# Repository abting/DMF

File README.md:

# DMF
DMF Arduino Software &amp; UI

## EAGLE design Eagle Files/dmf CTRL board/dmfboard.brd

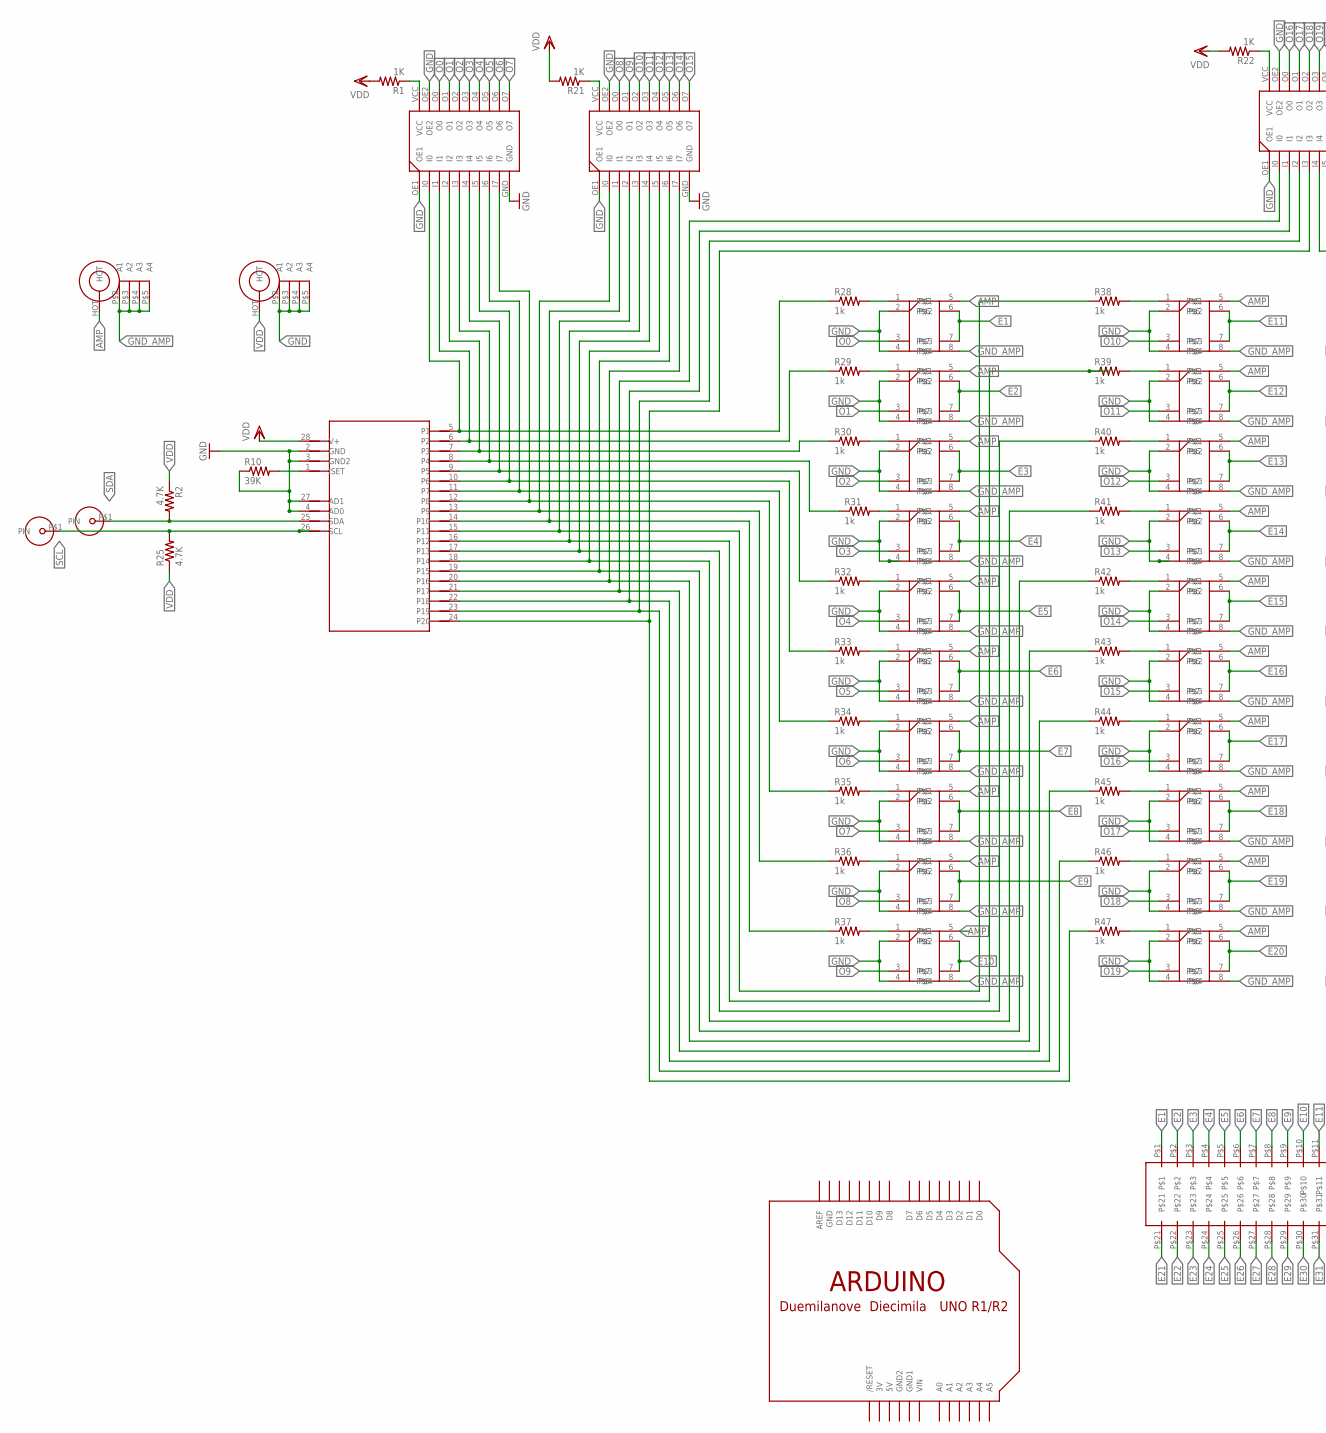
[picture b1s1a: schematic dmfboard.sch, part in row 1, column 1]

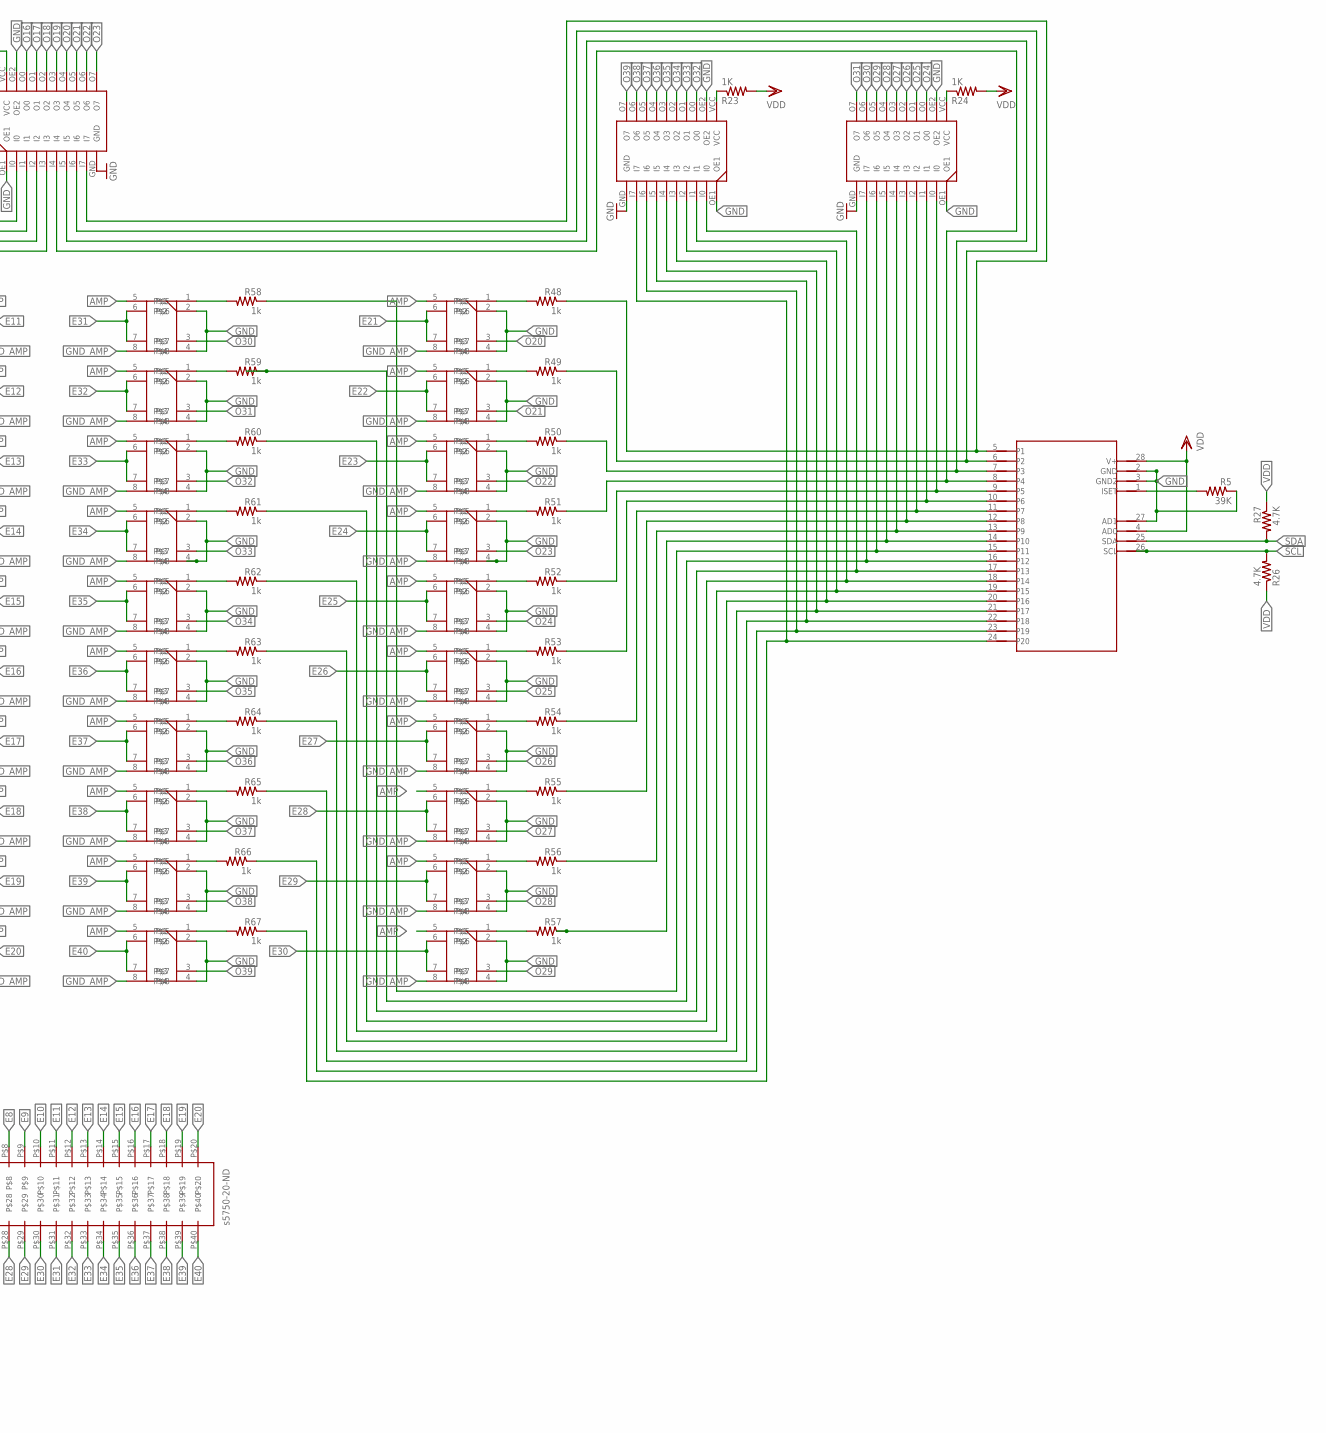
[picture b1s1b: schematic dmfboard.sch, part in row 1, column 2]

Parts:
+5V: BNC-BNC
AMP: BNC-BNC
INVERTOR1, INVERTOR2, INVERTOR3, INVERTOR4: 74AC540; SO20W
INVERTTOR5: 74AC540; SO20W
MAX1, MAX2: MAX7300; QSOP24
P1, P2, P3, P4, P5, P6, P7, P8, P9, P10, P11, P12, P13, P14, P15, P16, P17, P18, P19, P20, P21, P22, P23, P24, P25, P26, P27, P28, P29, P30, P31, P32, P33, P34, P35, P36, P37, P38, P39, P40: AQW21; AQW216EH
R1, R21, R22, R23, R24: 1K; M0805
R2, R25, R26, R27: 4.7K; M0805
R5, R10: 39K; M0805
R28, R29, R30, R31, R32, R33, R34, R35, R36, R37, R38, R39, R40, R41, R42, R43, R44, R45, R46, R47, R48, R49, R50, R51, R52, R53, R54, R55, R56, R57, R58, R59, R60, R61, R62, R63, R64, R65, R66, R67: 1k; M0805
SCL: TH_HOLE; TH_PIN
SDA: TH_HOLE; TH_PIN
U$1: ARDUINO-NODIM
U$50: S5750_20_ND40PIN_CONNECTOR; S5750-20_ND

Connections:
3V: U$1.3V
5V: U$1.5V
AMP: AMP.HOT, P1.5, P2.5, P3.5, P4.5, P5.5, P6.5, P7.5, P8.5, P9.5, P10.5, P11.5, P12.5, P13.5, P14.5, P15.5, P16.5, P17.5, P18.5, P19.5, P20.5, P21.5, P22.5, P23.5, P24.5, P25.5, P26.5, P27.5, P28.5, P29.5, P30.5, P31.5, P32.5, P33.5, P34.5, P35.5, P36.5, P37.5, P38.5, P39.5, P40.5
E1: P1.6, P1.7, U$50.P$1
E2: P2.6, P2.7, U$50.P$2
E3: P3.6, P3.7, U$50.P$3
E4: P4.6, P4.7, U$50.P$4
E5: P5.6, P5.7, U$50.P$5
E6: P6.6, P6.7, U$50.P$6
E7: P7.6, P7.7, U$50.P$7
E8: P8.6, P8.7, U$50.P$8
E9: P9.6, P9.7, U$50.P$9
E10: P10.6, P10.7, U$50.P$10
E11: P11.6, P11.7, U$50.P$11
E12: P12.6, P12.7, U$50.P$12
E13: P13.6, P13.7, U$50.P$13
E14: P14.6, P14.7, U$50.P$14
E15: P15.6, P15.7, U$50.P$15
E16: P16.6, P16.7, U$50.P$16
E17: P17.6, P17.7, U$50.P$17
E18: P18.6, P18.7, U$50.P$18
E19: P19.6, P19.7, U$50.P$19
E20: P20.6, P20.7, U$50.P$20
E21: P21.6, P21.7, U$50.P$21
E22: P22.6, P22.7, U$50.P$22
E23: P23.6, P23.7, U$50.P$23
E24: P24.6, P24.7, U$50.P$24
E25: P25.6, P25.7, U$50.P$25
E26: P26.6, P26.7, U$50.P$26
E27: P27.6, P27.7, U$50.P$27
E28: P28.6, P28.7, U$50.P$28
E29: P29.6, P29.7, U$50.P$29
E30: P30.6, P30.7, U$50.P$30
E31: P31.6, P31.7, U$50.P$31
E32: P32.6, P32.7, U$50.P$32
E33: P33.6, P33.7, U$50.P$33
E34: P34.6, P34.7, U$50.P$34
E35: P35.6, P35.7, U$50.P$35
E36: P36.6, P36.7, U$50.P$36
E37: P37.6, P37.7, U$50.P$37
E38: P38.6, P38.7, U$50.P$38
E39: P39.6, P39.7, U$50.P$39
E40: P40.6, P40.7, U$50.P$40
GND: +5V.P$2 (A1), +5V.P$3 (A2), +5V.P$4 (A3), +5V.P$5 (A4), INVERTOR1.GND, INVERTOR1.OE1, INVERTOR1.OE2, INVERTOR2.GND, INVERTOR2.OE1, INVERTOR2.OE2, INVERTOR3.GND, INVERTOR3.OE1, INVERTOR3.OE2, INVERTOR4.GND, INVERTOR4.OE1, INVERTOR4.OE2, INVERTTOR5.GND, INVERTTOR5.OE1, INVERTTOR5.OE2, MAX1.2 (GND), MAX1.3 (GND2), MAX1.4 (AD0), MAX1.27 (AD1), MAX2.2 (GND), MAX2.3 (GND2), MAX2.27 (AD1), P1.2, P1.4, P2.2, P2.4, P3.2, P3.4, P4.2, P4.4, P5.2, P5.4, P6.2, P6.4, P7.2, P7.4, P8.2, P8.4, P9.2, P9.4, P10.2, P10.4, P11.2, P11.4, P12.2, P12.4, P13.2, P13.4, P14.2, P14.4, P15.2, P15.4, P16.2, P16.4, P17.2, P17.4, P18.2, P18.4, P19.2, P19.4, P20.2, P20.4, P21.2, P21.4, P22.2, P22.4, P23.2, P23.4, P24.2, P24.4, P25.2, P25.4, P26.2, P26.4, P27.2, P27.4, P28.2, P28.4, P29.2, P29.4, P30.2, P30.4, P31.2, P31.4, P32.2, P32.4, P33.2, P33.4, P34.2, P34.4, P35.2, P35.4, P36.2, P36.4, P37.2, P37.4, P38.2, P38.4, P39.2, P39.4, P40.2, P40.4, R5.1, R10.1, U$1.GND
GND1: U$1.GND1
GND2: U$1.GND2
GND_AMP: AMP.P$2 (A1), AMP.P$3 (A2), AMP.P$4 (A3), AMP.P$5 (A4), P1.8, P2.8, P3.8, P4.8, P5.8, P6.8, P7.8, P8.8, P9.8, P10.8, P11.8, P12.8, P13.8, P14.8, P15.8, P16.8, P17.8, P18.8, P19.8, P20.8, P21.8, P22.8, P23.8, P24.8, P25.8, P26.8, P27.8, P28.8, P29.8, P30.8, P31.8, P32.8, P33.8, P34.8, P35.8, P36.8, P37.8, P38.8, P39.8, P40.8
unnamed: MAX2.1 (ISET), R5.2
unnamed: MAX1.1 (ISET), R10.2
unnamed: INVERTOR1.VCC, R1.1
unnamed: INVERTOR2.VCC, R21.1
unnamed: INVERTOR3.VCC, R22.1
unnamed: INVERTOR4.VCC, R23.1
unnamed: INVERTTOR5.VCC, R24.1
unnamed: P10.1, R37.2
unnamed: P9.1, R36.2
unnamed: P8.1, R35.2
unnamed: P7.1, R34.2
unnamed: P6.1, R33.2
unnamed: P5.1, R32.2
unnamed: P4.1, R31.2
unnamed: P3.1, R30.2
unnamed: P2.1, R29.2
unnamed: P1.1, R28.2
unnamed: P11.1, R38.2
unnamed: P12.1, R39.2
unnamed: P13.1, R40.2
unnamed: P14.1, R41.2
unnamed: P15.1, R42.2
unnamed: P16.1, R43.2
unnamed: P17.1, R44.2
unnamed: P18.1, R45.2
unnamed: P19.1, R46.2
unnamed: P20.1, R47.2
unnamed: INVERTOR1.I0, MAX1.5 (P1), R28.1
unnamed: INVERTOR1.I2, MAX1.7 (P3), R30.1
unnamed: INVERTOR1.I3, MAX1.8 (P4), R31.1
unnamed: INVERTOR1.I4, MAX1.9 (P5), R32.1
unnamed: INVERTOR1.I5, MAX1.10 (P6), R33.1
unnamed: INVERTOR1.I6, MAX1.11 (P7), R34.1
unnamed: INVERTOR1.I7, MAX1.12 (P8), R35.1
unnamed: INVERTOR2.I0, MAX1.13 (P9), R36.1
unnamed: INVERTOR2.I1, MAX1.14 (P10), R37.1
unnamed: INVERTOR2.I2, MAX1.15 (P11), R38.1
unnamed: INVERTOR2.I3, MAX1.16 (P12), R39.1
unnamed: INVERTOR2.I4, MAX1.17 (P13), R40.1
unnamed: INVERTOR2.I5, MAX1.18 (P14), R41.1
unnamed: INVERTOR2.I6, MAX1.19 (P15), R42.1
unnamed: INVERTOR2.I7, MAX1.20 (P16), R43.1
unnamed: INVERTOR3.I0, MAX1.21 (P17), R44.1
unnamed: INVERTOR3.I1, MAX1.22 (P18), R45.1
unnamed: INVERTOR3.I2, MAX1.23 (P19), R46.1
unnamed: INVERTOR3.I3, MAX1.24 (P20), R47.1
unnamed: INVERTOR1.I1, MAX1.6 (P2), R29.1
unnamed: P21.1, R48.2
unnamed: P22.1, R49.2
unnamed: P23.1, R50.2
unnamed: P24.1, R51.2
unnamed: P25.1, R52.2
unnamed: P26.1, R53.2
unnamed: P27.1, R54.2
unnamed: P28.1, R55.2
unnamed: P29.1, R56.2
unnamed: P30.1, R57.2
unnamed: INVERTTOR5.I0, MAX2.9 (P5), R52.1
unnamed: P31.1, R58.2
unnamed: P32.1, R59.2
unnamed: P33.1, R60.2
unnamed: P34.1, R61.2
unnamed: P35.1, R62.2
unnamed: P36.1, R63.2
unnamed: P37.1, R64.2
unnamed: P38.1, R65.2
unnamed: P39.1, R66.2
unnamed: P40.1, R67.2
unnamed: INVERTTOR5.I7, MAX2.16 (P12), R59.1
unnamed: INVERTTOR5.I1, MAX2.10 (P6), R53.1
unnamed: INVERTTOR5.I2, MAX2.11 (P7), R54.1
unnamed: INVERTTOR5.I3, MAX2.12 (P8), R55.1
unnamed: INVERTTOR5.I4, MAX2.13 (P9), R56.1
unnamed: INVERTTOR5.I5, MAX2.14 (P10), R57.1
unnamed: INVERTTOR5.I6, MAX2.15 (P11), R58.1
unnamed: INVERTOR4.I2, MAX2.19 (P15), R62.1
unnamed: INVERTOR4.I0, MAX2.17 (P13), R60.1
unnamed: INVERTOR4.I1, MAX2.18 (P14), R61.1
unnamed: INVERTOR4.I3, MAX2.20 (P16), R63.1
unnamed: INVERTOR4.I4, MAX2.21 (P17), R64.1
unnamed: INVERTOR4.I5, MAX2.22 (P18), R65.1
unnamed: INVERTOR4.I6, MAX2.23 (P19), R66.1
unnamed: INVERTOR4.I7, MAX2.24 (P20), R67.1
unnamed: INVERTOR3.I7, MAX2.5 (P1), R48.1
unnamed: INVERTOR3.I6, MAX2.6 (P2), R49.1
unnamed: INVERTOR3.I5, MAX2.7 (P3), R50.1
unnamed: INVERTOR3.I4, MAX2.8 (P4), R51.1
O0: INVERTOR1.O0, P1.3
O1: INVERTOR1.O1, P2.3
O2: INVERTOR1.O2, P3.3
O3: INVERTOR1.O3, P4.3
O4: INVERTOR1.O4, P5.3
O5: INVERTOR1.O5, P6.3
O6: INVERTOR1.O6, P7.3
O7: INVERTOR1.O7, P8.3
O8: INVERTOR2.O0, P9.3
O9: INVERTOR2.O1, P10.3
O10: INVERTOR2.O2, P11.3
O11: INVERTOR2.O3, P12.3
O12: INVERTOR2.O4, P13.3
O13: INVERTOR2.O5, P14.3
O14: INVERTOR2.O6, P15.3
O15: INVERTOR2.O7, P16.3
O16: INVERTOR3.O0, P17.3
O17: INVERTOR3.O1, P18.3
O18: INVERTOR3.O2, P19.3
O19: INVERTOR3.O3, P20.3
O20: INVERTOR3.O4, P21.3
O21: INVERTOR3.O5, P22.3
O22: INVERTOR3.O6, P23.3
O23: INVERTOR3.O7, P24.3
O24: INVERTTOR5.O0, P25.3
O25: INVERTTOR5.O1, P26.3
O26: INVERTTOR5.O2, P27.3
O27: INVERTTOR5.O3, P28.3
O28: INVERTTOR5.O4, P29.3
O29: INVERTTOR5.O5, P30.3
O30: INVERTTOR5.O6, P31.3
O31: INVERTTOR5.O7, P32.3
O32: INVERTOR4.O0, P33.3
O33: INVERTOR4.O1, P34.3
O34: INVERTOR4.O2, P35.3
O35: INVERTOR4.O3, P36.3
O36: INVERTOR4.O4, P37.3
O37: INVERTOR4.O5, P38.3
O38: INVERTOR4.O6, P39.3
O39: INVERTOR4.O7, P40.3
SCL: MAX1.26 (SCL), MAX2.26 (SCL), R25.2, R26.2, SCL.P$1
SDA: MAX1.25 (SDA), MAX2.25 (SDA), R2.2, R27.2, SDA.P$1
VDD: +5V.HOT, MAX1.28 (V+), MAX2.4 (AD0), MAX2.28 (V+), R1.2, R2.1, R21.2, R22.2, R23.2, R24.2, R25.1, R26.1, R27.1
VIN: U$1.VIN

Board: 2 copper layers, 104 parts (0 on the bottom side), 173 nets, no tracks yet.

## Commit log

2016-05-14 version 1.5
2016-05-16 Add files via upload
    added save and load functionality
2016-05-16 Add files via upload
    Working Code using MCP23017, inputs a string of instructions
    Improvements needed: optimize use of dynamic memory and recognize size of the string of instructions
2016-05-16 May 16th - Latest version
2016-05-17 Working arduino code for MCP
2016-05-20 Most recent MAX7300 code,
    is able to communicate with 2 MAX7300,
    includes the clearAll() function
2016-05-20 Changes made by Meko
2016-05-20 Functional with two Max7300s
2016-05-24 Add files via upload
    First version of the DMF components and patters, must be copied to DipTrace/My Libraries
2016-05-30 Array_Testing
2016-06-08 Please just make this work
2016-06-23 DMFGui With the autogen
2016-07-05 Deleted the extra unnecessary files
2016-07-06 32 bit version
    with comments
2016-07-10 changed the control board circuit, added jumper pins & one extra inverter
